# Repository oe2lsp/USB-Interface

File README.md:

# USB Interface

primitive and simple USB interfave for classic Ham Radio transceivers. 
- Brings the TRX to the 21st century and makes the operation of digi modes reliable and easy. 
- No more cables and adapters 
- KiCad based

Fits into Yaesu FT987 and FT817 (no Filters installed).

Components used:
- USB-Hub TUSB2036
- UART Interface: FT231XS
- Soundcard PCM2906[C] 

Down Side:
- only uses half of dynamic range at RX audio-chain as Yaesu TRX provide half of amplitude the IC can handle.

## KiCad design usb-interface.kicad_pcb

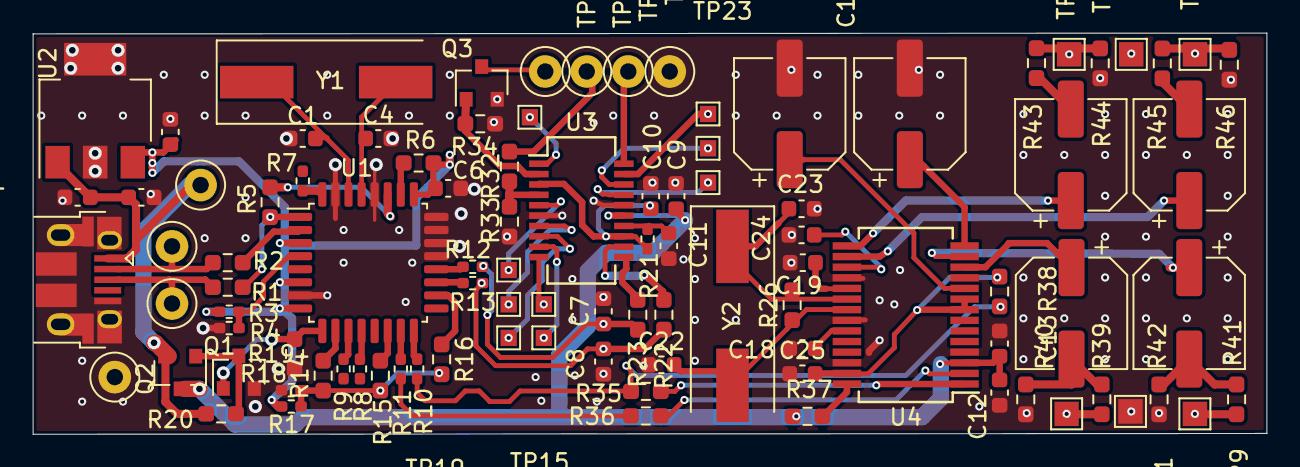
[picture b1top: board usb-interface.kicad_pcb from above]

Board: 2 copper layers, 75.5 x 24.5 mm, 97 parts (0 on the bottom side), 71 nets.

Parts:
C1, C2, C3, C4, C5, C6, C18, C19, C22, C23, C24, C25: C; C_0603_1608Metric
C7, C8: 47p; C_0603_1608Metric
C9, C10, C11, C13: 100n; C_0603_1608Metric
C12: 1u; C_0603_1608Metric
C14, C15, C16, C17, C20, C21: 10u; CP_Elec_6.3x5.9
J1: USB_B_Micro; USB_Micro-B_Amphenol_10103594-0001LF_Horizontal
Q1, Q3: Q_NMOS_GSD_BSS138; SOT-23
Q2: Q_PMOS_GSD_PMV74EPE; SOT-23
R1, R2, R6, R22, R23, R35, R36: 22E; R_0603_1608Metric_Pad0.98x0.95mm_HandSolder
R3, R7, R8, R9, R10, R11, R12, R13, R17, R21: 0E; R_0402_1005Metric_Pad0.72x0.64mm_HandSolder
R4: np; R_0402_1005Metric_Pad0.72x0.64mm_HandSolder
R5, R37, R38: 1k5; R_0603_1608Metric_Pad0.98x0.95mm_HandSolder
R14, R15, R16, R39, R41: 0E; R_0603_1608Metric_Pad0.98x0.95mm_HandSolder
R18: n.p.; R_0402_1005Metric_Pad0.72x0.64mm_HandSolder
R19, R20: R; R_0603_1608Metric_Pad0.98x0.95mm_HandSolder
R26: 1M; R_0603_1608Metric_Pad0.98x0.95mm_HandSolder
R32: 5.6k; R_0603_1608Metric_Pad0.98x0.95mm_HandSolder
R33: 10k; R_0603_1608Metric_Pad0.98x0.95mm_HandSolder
R34: 100k; R_0603_1608Metric_Pad0.98x0.95mm_HandSolder
R40, R42: np; R_0603_1608Metric_Pad0.98x0.95mm_HandSolder
R43, R45: 3k3; R_0603_1608Metric_Pad0.98x0.95mm_HandSolder
R44, R46: 470E; R_0603_1608Metric_Pad0.98x0.95mm_HandSolder
TP1, TP2, TP3, TP4, TP5, TP6, TP7, TP8: TestPoint; TestPoint_Loop_D1.80mm_Drill1.0mm_Beaded
TP9, TP10, TP11, TP12, TP13, TP14: TestPoint; TestPoint_Pad_1.5x1.5mm
TP15, TP16, TP17, TP18, TP19, TP20, TP21, TP22, TP23: TestPoint; TestPoint_Pad_1.0x1.0mm
U1: TUSB2036; LQFP-32_7x7mm_P0.8mm
U2: LF33; SOT-223-3_TabPin2
U3: FT231XS; SSOP-20_3.9x8.7mm_P0.635mm
U4: PCM2906(C); SSOP-28_5.3x10.2mm_P0.65mm
Y1: 6MHz; Crystal_SMD_HC49-SD
Y2: 12MHz; Crystal_SMD_HC49-SD

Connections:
+3.3VP: C10.1, R21.2, U3.3 (VCCIO), U3.13 (3V3OUT)
+3V3: C5.1, C6.1, R3.2, R6.1, R17.1, U1.3 (VCC), U1.6 (EEDATA/~GANGED), U1.8 (~BUSPWR), U1.25 (VCC), U2.3 (VO)
+5P: C2.1, C3.1, J1.1 (VBUS), Q2.2 (S), R20.2, TP1.1, U2.1 (VI)
+5V: C9.1, C12.1, C13.1, Q2.3 (D), R37.2, U3.15 (VCC), U4.3 (V_BUS)
/FTDI/CBUS0: TP20.1, U3.18 (CBUS0)
/FTDI/CBUS1: TP21.1, U3.17 (CBUS1)
/FTDI/CBUS2: TP22.1, U3.10 (CBUS2)
/FTDI/CBUS3: TP23.1, U3.19 (CBUS3)
/FTDI/CTS: TP15.1, U3.9 (~CTS)
/FTDI/DCD: TP18.1, U3.8 (~DCD)
/FTDI/DSR: TP17.1, U3.7 (~DSR)
/FTDI/DTR: TP16.1, U3.1 (~DTR)
/FTDI/PTT: Q3.3 (D), TP7.1
/FTDI/RI: TP19.1, U3.5 (~RI)
/FTDI/RTS: Q3.1 (G), R34.1, U3.2 (~RTS)
/FTDI/RXD: R32.1, TP6.1
/FTDI/TXD: TP5.1, U3.20 (TXD)
/soundcard2/I_L: R39.2, TP10.1
/soundcard2/I_R: R41.2, TP9.1
/soundcard2/O_L: R45.1, R46.2, TP12.1
/soundcard2/O_R: R43.1, R44.2, TP13.1
/soundcard2/VDD_I: C25.2, R38.2, U4.8 (SEL0), U4.9 (SEL1), U4.27 (VDD_I)
DM2: R11.1, R36.2
DM3: C8.1, R13.1, R22.2
DP2: R10.1, R35.2, R38.1
DP3: C7.1, R12.2, R23.2
GND: C1.2, C2.2, C3.2, C4.2, C5.2, C6.2, C7.2, C8.2, C9.2, C10.2, C11.2, C12.2, C13.2, C14.2, C17.2, C18.1, C19.1, C22.1, C23.1, C24.1, C25.1, J1.5 (GND), J1.6 (Shield), Q1.2 (S), Q3.2 (S), R4.2, R18.1, R19.1, R33.2, R34.2, R40.1, R42.1, R44.1, R46.1, TP2.1, TP8.1, TP11.1, U1.7 (GND), U1.21 (~OCPROT/~PWRSW), U1.22 (NPINT0), U1.23 (NPINT1), U1.24 (~NP3), U1.28 (GND), U1.31 (MODE), U2.2 (GND), U3.6 (GND), U3.16 (GND), U4.4 (DGNDU), U4.11 (AGNDC), U4.18 (AGNDP), U4.22 (AGNDX), U4.26 (DGND)
unnamed: C1.1, U1.30 (XTAL1/CLK48), Y1.1
unnamed: C4.1, U1.29 (XTAL2), Y1.2
unnamed: C11.1, R21.1, U3.14 (~RESET)
unnamed: C14.1, U4.10 (VCCI)
unnamed: C15.1, U4.12 (V_IN_L)
unnamed: C15.2, R39.1, R40.2
unnamed: C16.1, U4.13 (V_IN_R)
unnamed: C16.2, R41.1, R42.2
unnamed: C17.1, U4.14 (V_COM)
unnamed: C18.2, U4.23 (VCC_XI)
unnamed: C19.2, U4.19 (VCC_P2I)
unnamed: C20.1, U4.16 (V_OUT_L)
unnamed: C20.2, R45.2
unnamed: C21.1, U4.15 (V_OUT_R)
unnamed: C21.2, R43.2
unnamed: C22.2, R26.1, U4.21 (XTI), Y2.2
unnamed: C23.2, R26.2, U4.20 (XTO), Y2.1
unnamed: C24.2, U4.17 (VCC_P1I)
unnamed: J1.2 (D-), R2.2, TP4.1
unnamed: J1.3 (D+), R1.2, TP3.1
unnamed: Q1.1 (G), R19.2, U1.9 (~PWRON1)
unnamed: Q1.3 (D), Q2.1 (G), R20.1
unnamed: R1.1, R5.2, U1.1 (DP0)
unnamed: R2.1, U1.2 (DM0)
unnamed: R3.1, R4.1, U1.4 (~RESET)
unnamed: R5.1, U1.27 (DP0PUR)
unnamed: R6.2, U1.26 (~EXTMEM)
unnamed: R7.2, U1.32 (SUSPND)
unnamed: R8.2, U1.12 (DP1)
unnamed: R9.2, U1.11 (DM1)
unnamed: R10.2, U1.16 (DP2)
unnamed: R11.2, U1.15 (DM2)
unnamed: R12.1, U1.20 (DP3)
unnamed: R13.2, U1.19 (DM3)
unnamed: R14.1, R15.1, R16.1, R17.2, R18.2
unnamed: R14.2, U1.10 (~OVRCUR1)
unnamed: R15.2, U1.14 (~OVRCUR2)
unnamed: R16.2, U1.18 (~OVRCUR3)
unnamed: R22.1, U3.12 (USBDM)
unnamed: R23.1, U3.11 (USBDP)
unnamed: R32.2, R33.1, U3.4 (RXD)
unnamed: R35.1, U4.1 (D+)
unnamed: R36.1, U4.2 (D-)
unnamed: R37.1, U4.28 (SSPND)

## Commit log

2023-10-30 Create README.md
    inital commit
2023-10-30 ft817
